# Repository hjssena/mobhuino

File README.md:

# mobhuino
Placa de baixo custo baseada no Arduino

Versão Atual: 3.1 (01/11/2016)

Autor: Hamilton Sena

Site: http://mobhuino.devidaasuaideia.com.br

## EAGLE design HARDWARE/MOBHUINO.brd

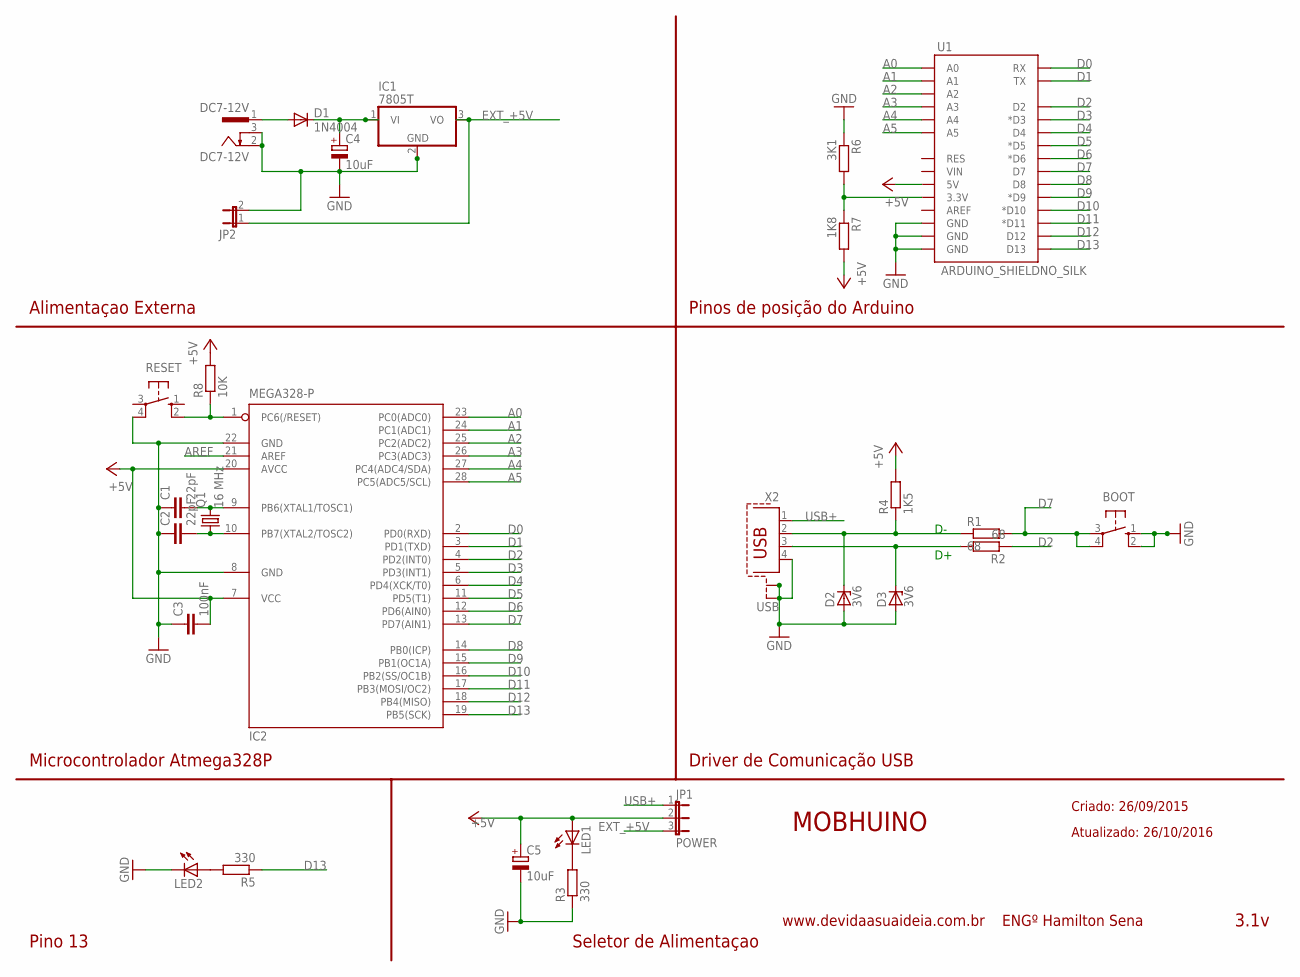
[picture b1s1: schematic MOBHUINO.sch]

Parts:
BOOT: 10-XX; B3F-10XX
C1, C2: 22pF; C025-024X044
C3: 100nF; C050-024X044
C4, C5: 10uF; E2,5-6
D1: 1N4004; DO41-10
D2, D3: 3V6; DO34Z7
DC7-12V: DC7-12V; 733980-62
IC1: 7805T; TO220H
IC2: MEGA328-P; DIL28-3
JP1: POWER; JP2
JP2: JP1E; JP1
LED1, LED2: LED3MM
Q1: 16 MHz; HC49/S
R1, R2: 68; 0207/7
R3, R5: 330; 0207/7
R4: 1K5; 0207/7
R6: 3K1; 0207/7
R7: 1K8; 0207/7
R8: 10K; 0207/7
RESET: 10-XX; B3F-10XX
U1: ARDUINO_SHIELDNO_SILK; DUEMILANOVE_VIAS
X2: USB; PN61729-S

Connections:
+5V: C3.2, C5.+, IC2.7 (VCC), IC2.20 (AVCC), JP1.2, LED1.A, R4.2, R7.2, R8.2, U1.5V
A0: IC2.23 (PC0(ADC0)), U1.A0
A1: IC2.24 (PC1(ADC1)), U1.A1
A2: IC2.25 (PC2(ADC2)), U1.A2
A3: IC2.26 (PC3(ADC3)), U1.A3
A4: IC2.27 (PC4(ADC4/SDA)), U1.A4
A5: IC2.28 (PC5(ADC5/SCL)), U1.A5
AREF: IC2.21 (AREF)
D0: IC2.2 (PD0(RXD)), U1.RX
D1: IC2.3 (PD1(TXD)), U1.TX
D2: IC2.4 (PD2(INT0)), R2.1, U1.D2
D3: IC2.5 (PD3(INT1)), U1.D3 (*D3)
D4: IC2.6 (PD4(XCK/T0)), U1.D4
D5: IC2.11 (PD5(T1)), U1.D5 (*D5)
D6: IC2.12 (PD6(AIN0)), U1.D6 (*D6)
D7: BOOT.3, BOOT.4 (P1), IC2.13 (PD7(AIN1)), R1.2, U1.D7
D8: IC2.14 (PB0(ICP)), U1.D8
D9: IC2.15 (PB1(OC1A)), U1.D9 (*D9)
D10: IC2.16 (PB2(SS/OC1B)), U1.D10 (*D10)
D11: IC2.17 (PB3(MOSI/OC2)), U1.D11 (*D11)
D12: IC2.18 (PB4(MISO)), U1.D12
D13: IC2.19 (PB5(SCK)), R5.1, U1.D13
D-: D2.C, R1.1, R4.1, X2.2
EXT_+5V: IC1.3 (VO), JP1.3, JP2.1
GND: BOOT.1 (S), BOOT.2 (S1), C1.1, C2.1, C3.1, C4.-, C5.-, D2.A, D3.A, DC7-12V.2, DC7-12V.3, IC1.2 (GND), IC2.8 (GND), IC2.22 (GND), JP2.2, LED2.K (C), R3.1, R6.1, RESET.4 (P1), U1.GND@0 (GND), U1.GND@1 (GND), U1.GND@2 (GND), X2.4, X2.S1, X2.S2
unnamed: D1.A, DC7-12V.1
unnamed: R6.2, R7.1, U1.3.3V
unnamed: C1.2, IC2.9 (PB6(XTAL1/TOSC1)), Q1.2
unnamed: C2.2, IC2.10 (PB7(XTAL2/TOSC2)), Q1.1
unnamed: IC2.1 (PC6(/RESET)), R8.1, RESET.2 (S1)
unnamed: LED2.A, R5.2
unnamed: D3.C, R2.2, X2.3
unnamed: LED1.K (C), R3.2
unnamed: C4.+, D1.C, IC1.1 (VI)
USB+: JP1.1, X2.1

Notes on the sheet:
MOBHUINO
www.devidaasuaideia.com.br
3.1v
Criado: 26/09/2015
Atualizado: 26/10/2016
Alimentaçao Externa
Pinos de posição do Arduino
Microcontrolador Atmega328P
Driver de Comunicação USB
Pino 13
Seletor de Alimentaçao
ENGº Hamilton Sena

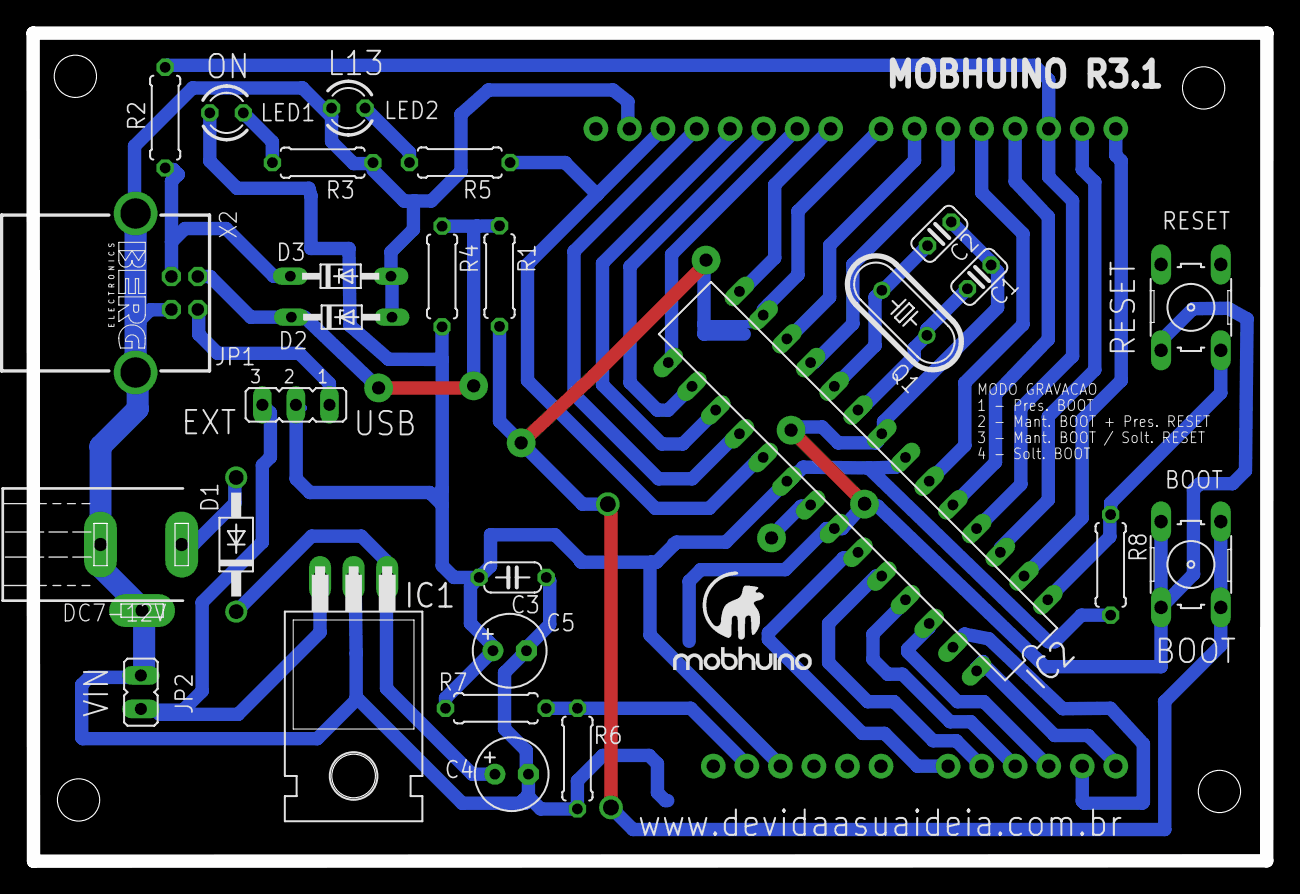
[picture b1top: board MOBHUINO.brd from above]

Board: 2 copper layers, 93.4 x 62.7 mm, 28 parts (0 on the bottom side), 34 nets.

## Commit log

2016-11-24 Commit inicial - Adicionado os arquivos fontes SCH e BRD criados no sosftware EAGLE
2016-11-24 - ADD: Drivers - ADD: BIBLIOTECAS HIDSerial - ADD: Ferramentas (SERIAL e ARDUBLOCK)
2017-04-06 - Inserção da malha de terra - Melhorado algumas trilhas - Modificado a linha de corte externa mais para mais grossa
2017-04-06 - Atualizado logo do Mobhuino
2017-04-06 - Atualizado a data de atualização do circuito

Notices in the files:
parts and their libraries:
SparkFun-Boards: Licensing: Creative Commons ShareAlike 4.0 International - https://creativecommons.org/licenses/by-sa/4.0
